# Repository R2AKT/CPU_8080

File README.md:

License addendum - https://github.com/R2AKT/CPU_8080/blob/main/Addendum.txt
# CPU_8080

580VM80a (8080a) CPU board.
For Mega-80 (Mega-580) DIY 8-bit micro-computer - https://github.com/R2AKT/Mega-80.

The board includes:
- processor = 580BM80a (8080a);
- clock generator = 580GF24 (8224); 
- data and control bus controller = 580BK28/38 (8228/8238);
- address bus buffer's = 2x580VA86 = (8286).

* There is a project option with the replacement of 580IR82/580V86 with 555AP6 (74LS245).

The board does not contain memory!

Status: tested in conjunction with an 8k linear memory module at a frequency of up to 3 MHz (quartz resonator 27 MHz).

Процессорная плата 580ВМ80а.
Для самодельной 8-битной микро-ЭВМ - https://github.com/R2AKT/Mega-80.

Плата содержит:
- процессор = 580ВМ80а;
- тактовый генератор = 580ГФ24;
- контроллер шины данных и управления = 580ВК28/38;
- буфер шины адреса = 2x580ВА86.

* Имеется вариант проекта с заменой 580ИР82/580ВА86 на 555АП6.

Плата не содержит память!

Статус: проверено совместно с модулем линейной памяти 8к на частоте до 3 МГц (кварцевый резонатор 27 МГц).

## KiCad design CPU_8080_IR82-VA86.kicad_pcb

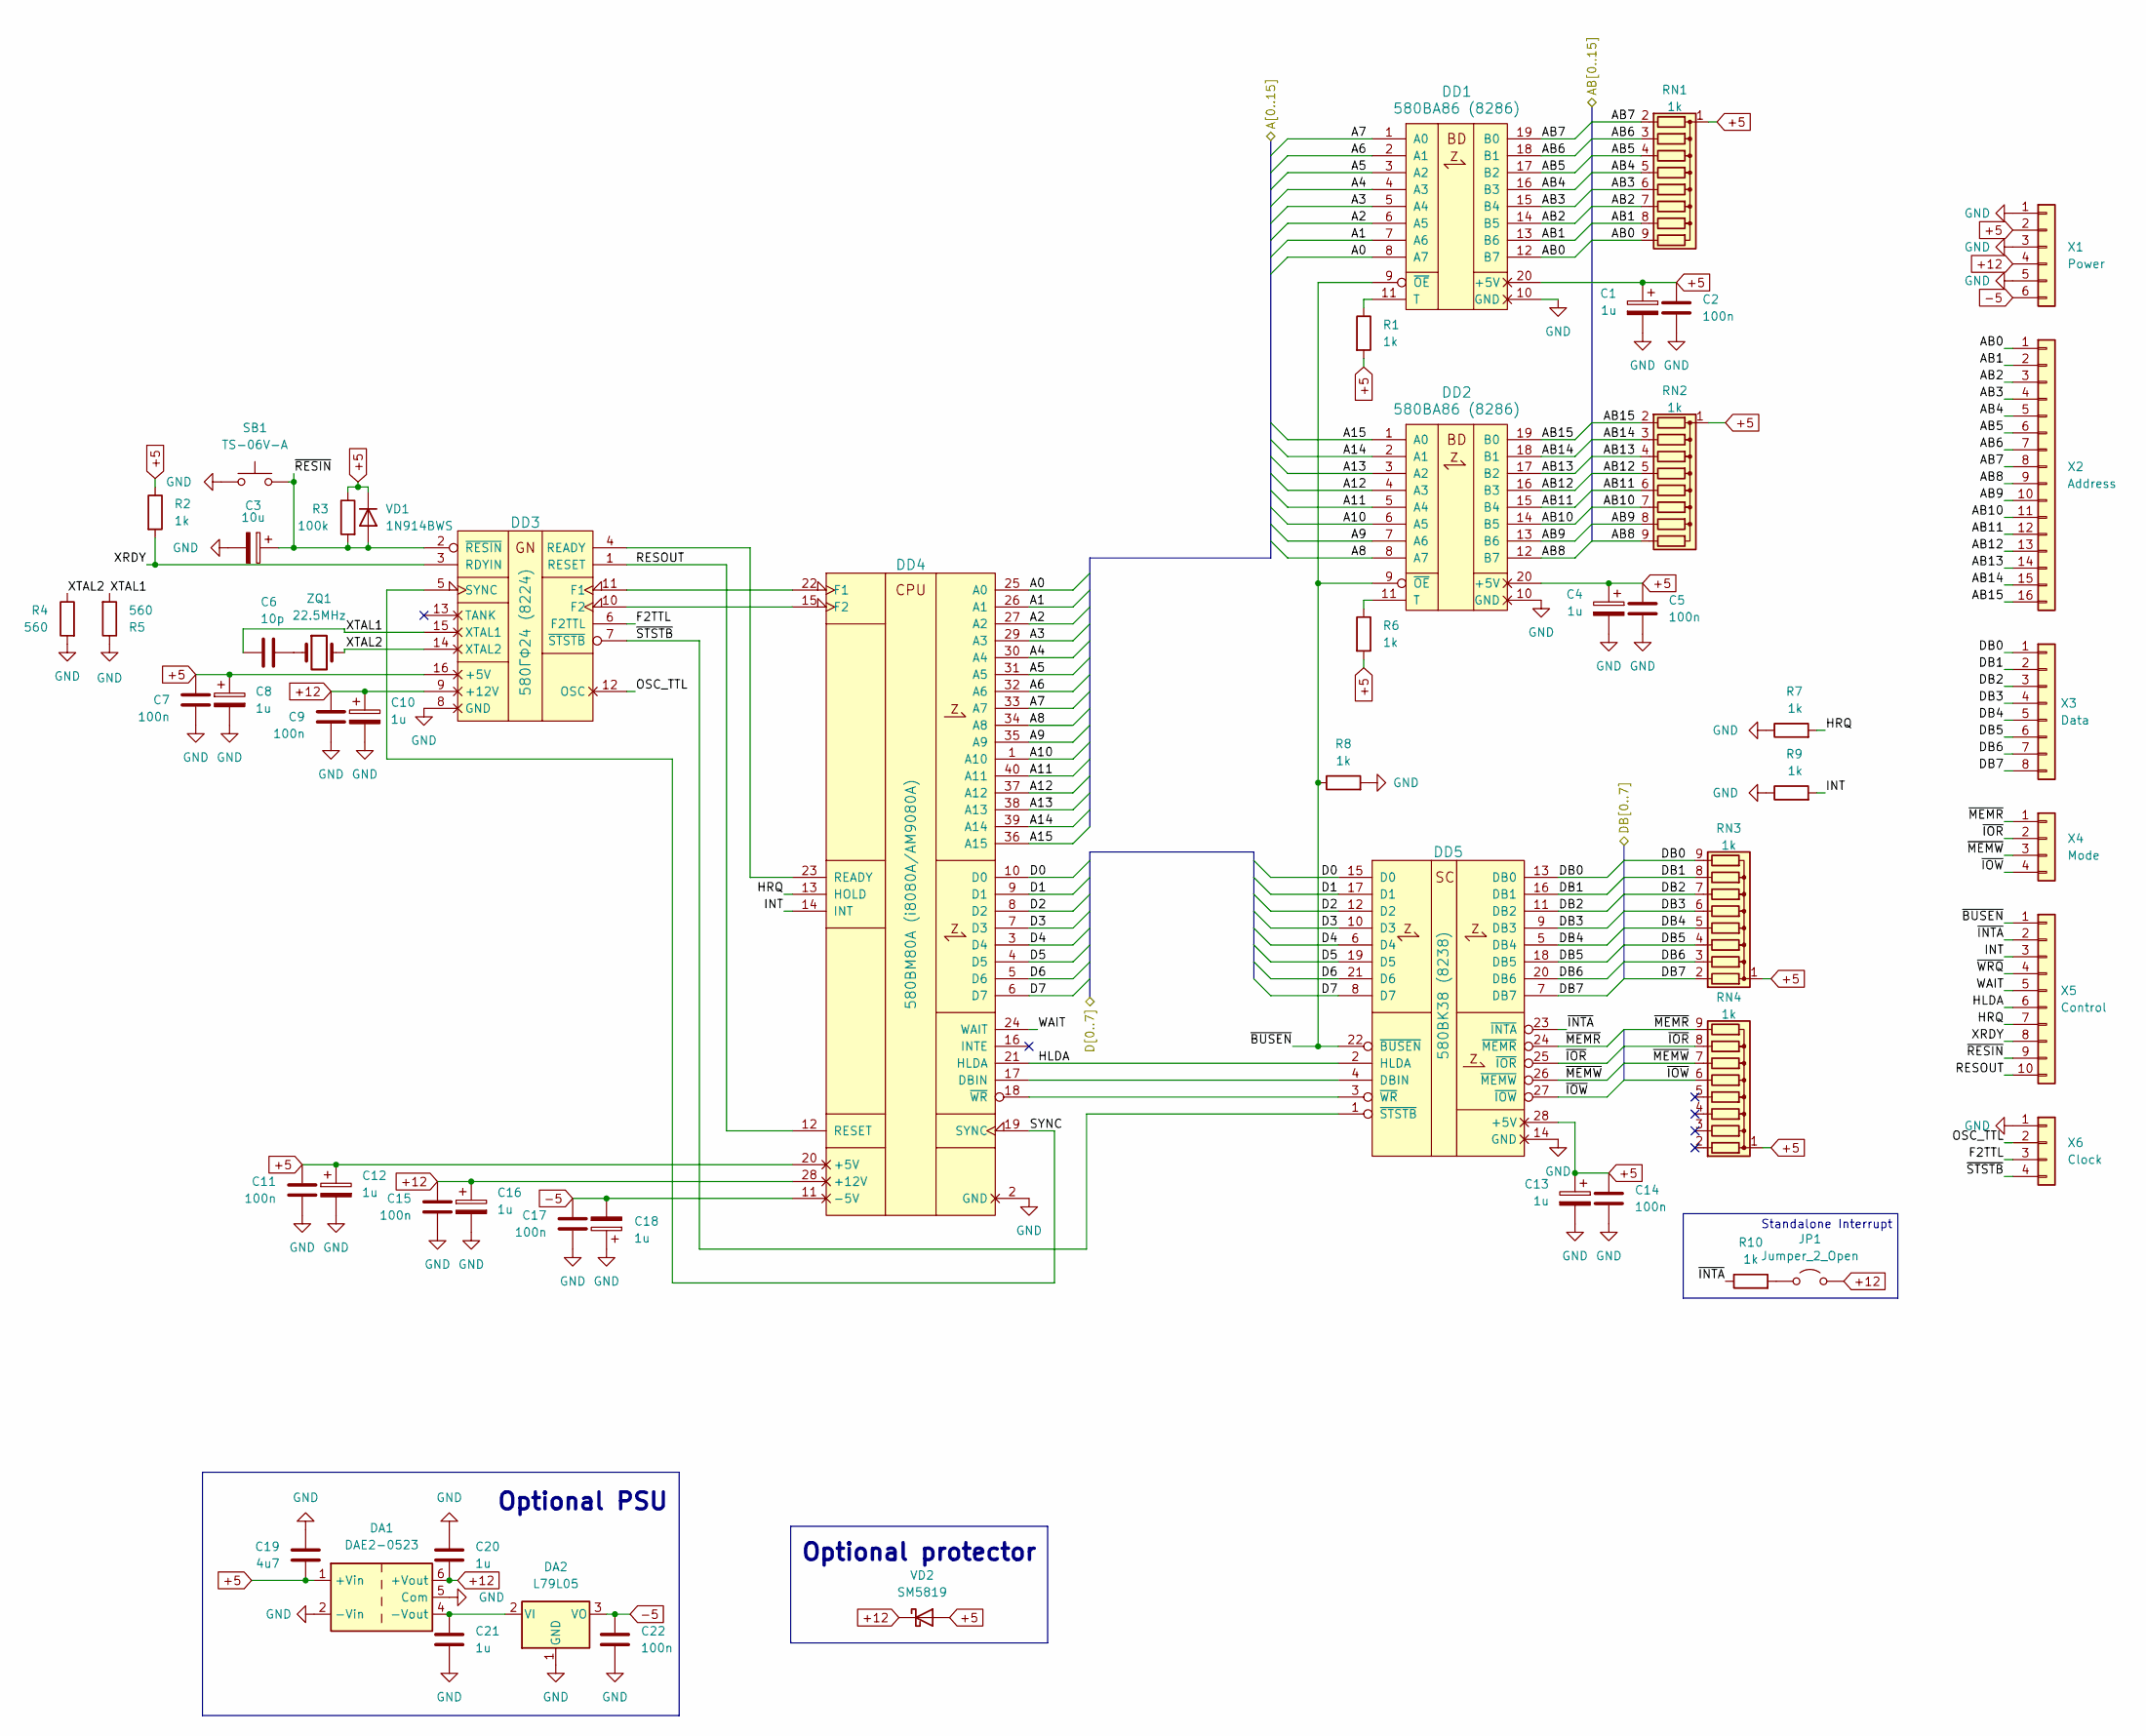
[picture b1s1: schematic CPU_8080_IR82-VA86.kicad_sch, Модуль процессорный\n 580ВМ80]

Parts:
C1, C4, C8, C10, C12, C13, C16, C18: 1u; CP_EIA-3216-18_Kemet-A_Pad1.58x1.35mm_HandSolder
C2, C5, C7, C9, C11, C14, C15, C17, C22: 100n; C_0805_2012Metric_Pad1.18x1.45mm_HandSolder
C3: 10u; CP_EIA-3216-18_Kemet-A_Pad1.58x1.35mm_HandSolder
C6: 10p; C_0805_2012Metric_Pad1.18x1.45mm_HandSolder
C19: 4u7; C_0805_2012Metric_Pad1.18x1.45mm_HandSolder
C20, C21: 1u; C_0805_2012Metric_Pad1.18x1.45mm_HandSolder
DA1: DAE2-0523; Converter_DCDC_TRACO_TBA1-xxxxE_Dual_THT
DA2: L79L05; SOT-89-3
DD1, DD2: 580ВА86 (8286); DIP-20_W7.62mm_Socket_LongPads
DD3: 580ГФ24 (8224); DIP-16_W7.62mm_Socket_LongPads
DD4: 580ВМ80A (i8080A/AM9080A); DIP-40_W15.24mm_Socket_LongPads
DD5: 580ВК38 (8238); DIP-28_W15.24mm_Socket_LongPads
JP1: Jumper_2_Open; SolderJumper-2_P1.3mm_Open_RoundedPad1.0x1.5mm
R1, R2, R6, R7, R8, R9, R10: 1k; R_0805_2012Metric_Pad1.20x1.40mm_HandSolder
R3: 100k; R_0805_2012Metric_Pad1.20x1.40mm_HandSolder
R4, R5: 560; R_0805_2012Metric_Pad1.20x1.40mm_HandSolder
RN1, RN2, RN3, RN4: 1k; R_Array_SIP9
SB1: TS-06V-A; SW_PUSH_6mm
VD1: 1N914BWS; D_SOD-323_HandSoldering
VD2: SM5819; D_SOD-123
X1: Power; PinHeader_1x06_P2.54mm_Vertical
X2: Address; PinHeader_1x16_P2.54mm_Vertical
X3: Data; PinHeader_1x08_P2.54mm_Vertical
X4: Mode; PinHeader_1x04_P2.54mm_Vertical
X5: Control; PinHeader_1x10_P2.54mm_Vertical
X6: Clock; PinHeader_1x04_P2.54mm_Vertical
ZQ1: 22.5MHz; Crystal_HC49-U_Vertical

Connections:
+5: C1.1, C2.1, C4.1, C5.1, C7.1, C8.1, C11.1, C12.1, C13.1, C14.1, C19.1, DA1.1 (+Vin), DD1.20 (+5V), DD2.20 (+5V), DD3.16 (+5V), DD4.20 (+5V), DD5.28 (+5V), R1.2, R2.1, R3.1, R6.2, RN1.1 (common), RN2.1 (common), RN3.1 (common), RN4.1 (common), VD1.1 (K), VD2.2 (A), X1.2
+12: C9.1, C10.1, C15.1, C16.1, C20.1, DA1.6 (+Vout), DD3.9 (+12V), DD4.28 (+12V), JP1.2 (B), VD2.1 (K), X1.4
-5: C17.1, C18.2, C22.1, DA2.3 (VO), DD4.11 (-5V), X1.6
/A0: DD1.8 (A7), DD4.25 (A0)
/A1: DD1.7 (A6), DD4.26 (A1)
/A2: DD1.6 (A5), DD4.27 (A2)
/A3: DD1.5 (A4), DD4.29 (A3)
/A4: DD1.4 (A3), DD4.30 (A4)
/A5: DD1.3 (A2), DD4.31 (A5)
/A6: DD1.2 (A1), DD4.32 (A6)
/A7: DD1.1 (A0), DD4.33 (A7)
/A8: DD2.8 (A7), DD4.34 (A8)
/A9: DD2.7 (A6), DD4.35 (A9)
/A10: DD2.6 (A5), DD4.1 (A10)
/A11: DD2.5 (A4), DD4.40 (A11)
/A12: DD2.4 (A3), DD4.37 (A12)
/A13: DD2.3 (A2), DD4.38 (A13)
/A14: DD2.2 (A1), DD4.39 (A14)
/A15: DD2.1 (A0), DD4.36 (A15)
/AB0: DD1.12 (B7), RN1.9 (R8), X2.1
/AB1: DD1.13 (B6), RN1.8 (R7), X2.2
/AB2: DD1.14 (B5), RN1.7 (R6), X2.3
/AB3: DD1.15 (B4), RN1.6 (R5), X2.4
/AB4: DD1.16 (B3), RN1.5 (R4), X2.5
/AB5: DD1.17 (B2), RN1.4 (R3), X2.6
/AB6: DD1.18 (B1), RN1.3 (R2), X2.7
/AB7: DD1.19 (B0), RN1.2 (R1), X2.8
/AB8: DD2.12 (B7), RN2.9 (R8), X2.9
/AB9: DD2.13 (B6), RN2.8 (R7), X2.10
/AB10: DD2.14 (B5), RN2.7 (R6), X2.11
/AB11: DD2.15 (B4), RN2.6 (R5), X2.12
/AB12: DD2.16 (B3), RN2.5 (R4), X2.13
/AB13: DD2.17 (B2), RN2.4 (R3), X2.14
/AB14: DD2.18 (B1), RN2.3 (R2), X2.15
/AB15: DD2.19 (B0), RN2.2 (R1), X2.16
/D0: DD4.10 (D0), DD5.15 (D0)
/D1: DD4.9 (D1), DD5.17 (D1)
/D2: DD4.8 (D2), DD5.12 (D2)
/D3: DD4.7 (D3), DD5.10 (D3)
/D4: DD4.3 (D4), DD5.6 (D4)
/D5: DD4.4 (D5), DD5.19 (D5)
/D6: DD4.5 (D6), DD5.21 (D6)
/D7: DD4.6 (D7), DD5.8 (D7)
/DB0: DD5.13 (DB0), RN3.9 (R8), X3.1
/DB1: DD5.16 (DB1), RN3.8 (R7), X3.2
/DB2: DD5.11 (DB2), RN3.7 (R6), X3.3
/DB3: DD5.9 (DB3), RN3.6 (R5), X3.4
/DB4: DD5.5 (DB4), RN3.5 (R4), X3.5
/DB5: DD5.18 (DB5), RN3.4 (R3), X3.6
/DB6: DD5.20 (DB6), RN3.3 (R2), X3.7
/DB7: DD5.7 (DB7), RN3.2 (R1), X3.8
/F2TTL: DD3.6 (F2TTL), X6.3
/HLDA: DD4.21 (HLDA), DD5.2 (HLDA), X5.6
/HRQ: DD4.13 (HOLD), R7.2, X5.7
/INT: DD4.14 (INT), R9.2, X5.3
/OSC_TTL: DD3.12 (OSC), X6.2
/RESOUT: DD3.1 (RESET), DD4.12 (RESET), X5.10
/SYNC: DD3.5 (SYNC), DD4.19 (SYNC)
/WAIT: DD4.24 (WAIT), X5.5
/XRDY: DD3.3 (RDYIN), R2.2, X5.8
/XTAL1: C6.2, DD3.15 (XTAL1), R5.2
/XTAL2: DD3.14 (XTAL2), R4.1, ZQ1.2
/~BUSEN: DD1.9 (~OE), DD2.9 (~OE), DD5.22 (~BUSEN), R8.1, X5.1
/~INTA: DD5.23 (~INTA), R10.1, X5.2
/~IOR: DD5.25 (~IOR), RN4.8 (R7), X4.2
/~IOW: DD5.27 (~IOW), RN4.6 (R5), X4.4
/~MEMR: DD5.24 (~MEMR), RN4.9 (R8), X4.1
/~MEMW: DD5.26 (~MEMW), RN4.7 (R6), X4.3
/~RESIN: C3.1, DD3.2 (~RESIN), R3.2, SB1.2, VD1.2 (A), X5.9
/~STSTB: DD3.7 (~STSTB), DD5.1 (~STSTB), X6.4
/~WRQ: X5.4
GND: C1.2, C2.2, C3.2, C4.2, C5.2, C7.2, C8.2, C9.2, C10.2, C11.2, C12.2, C13.2, C14.2, C15.2, C16.2, C17.2, C18.1, C19.2, C20.2, C21.2, C22.2, DA1.2 (-Vin), DA1.5 (Com), DA2.1 (GND), DD1.10 (GND), DD2.10 (GND), DD3.8 (GND), DD4.2 (GND), DD5.14 (GND), R4.2, R5.1, R7.1, R8.2, R9.1, SB1.1, X1.1, X1.3, X1.5, X6.1
unnamed: C6.1, ZQ1.1
unnamed: C21.1, DA1.4 (-Vout), DA2.2 (VI)
unnamed: DD1.11 (T), R1.1
unnamed: DD2.11 (T), R6.1
unnamed: DD3.11 (F1), DD4.22 (F1)
unnamed: DD3.10 (F2), DD4.15 (F2)
unnamed: DD3.4 (READY), DD4.23 (READY)
unnamed: DD4.17 (DBIN), DD5.4 (DBIN)
unnamed: DD4.18 (~WR), DD5.3 (~WR)
unnamed: JP1.1 (A), R10.2

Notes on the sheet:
Standalone Interrupt
Optional PSU
Optional protector

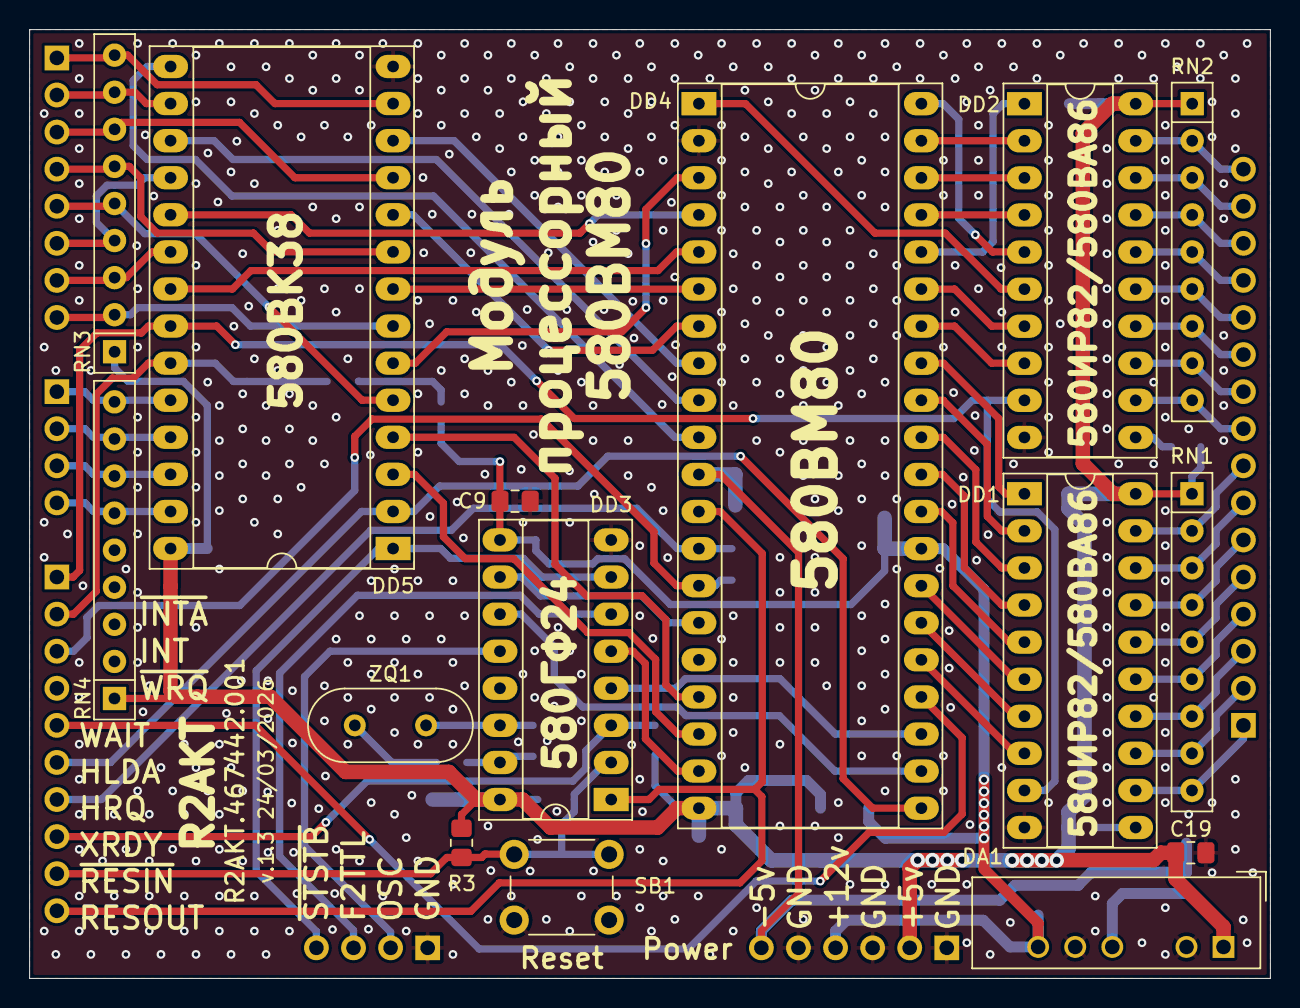
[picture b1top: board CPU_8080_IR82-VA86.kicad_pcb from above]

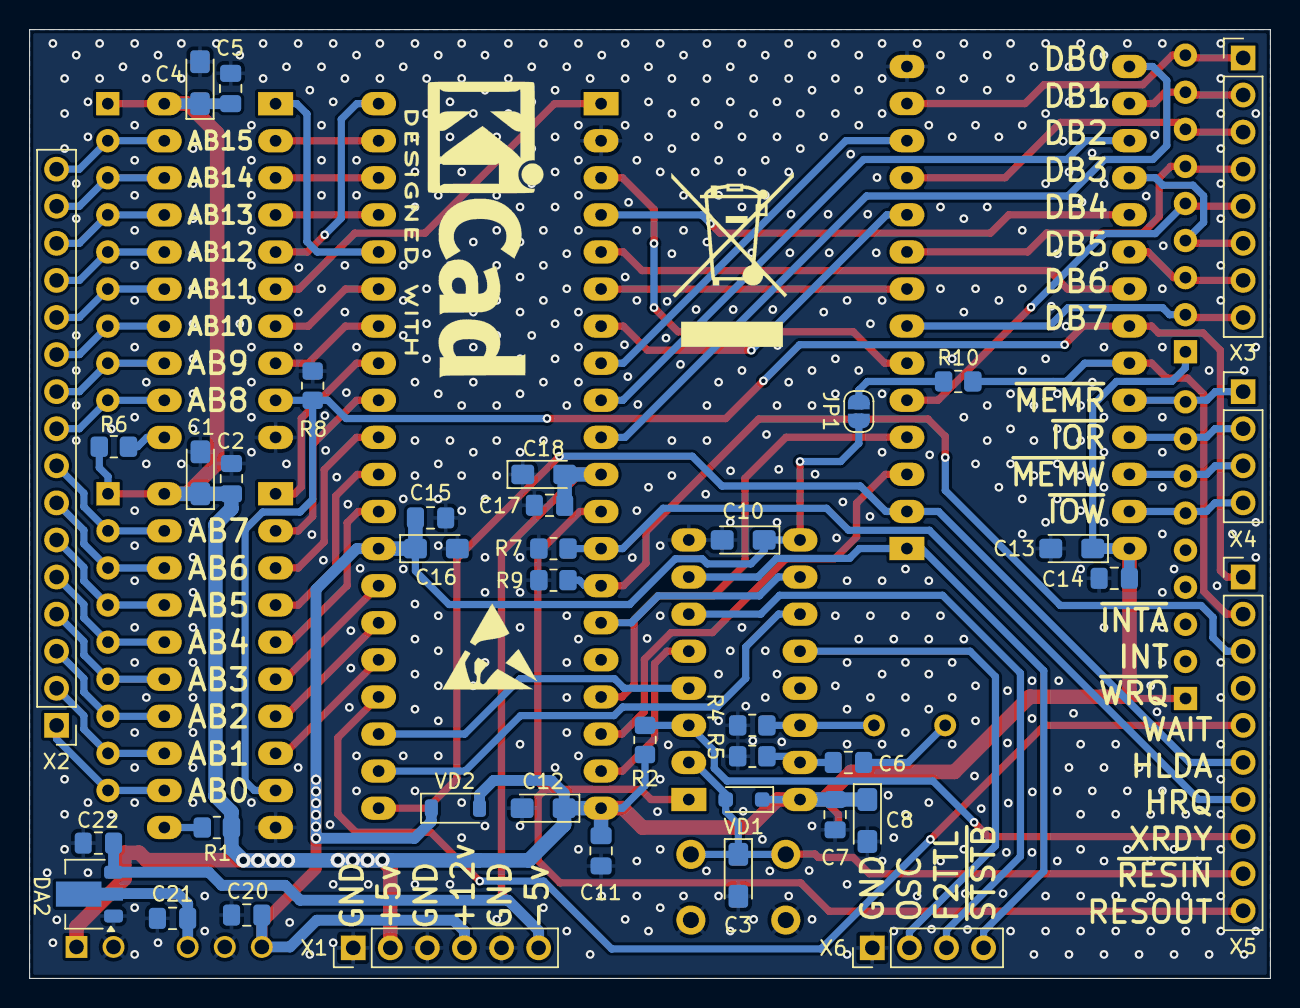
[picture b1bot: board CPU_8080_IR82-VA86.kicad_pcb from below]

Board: 2 copper layers, 85.0 x 65.0 mm, 54 parts (39 on the bottom side), 81 nets.

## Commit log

2026-01-26 Add files via upload
    Minor fix.
    Незначительные правки.
2026-01-26 Add files via upload
    An option has been added to replace the 580IR82/580VA86 with 555AP6 (74LS245). The version may lag behind the main project.
    Добавлен вариант с заменой 580ИР82/580ВА86 на 555АП6. Версия может отставать от основного проекта.

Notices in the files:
README.md:
License: MIT
